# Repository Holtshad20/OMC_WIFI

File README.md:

# OMC WIFI

Proyecto de dispositivo medidor/protector conectado a una red a través de Wi-Fi y monitoreado con un servidor inicialmente interno a la red.

## Dispositivo medidor

### Hardware
Versión actual: 1.0\
Estado: Diseño PCB a la espera de enviar a fábrica.

**Listo**
- Diseño Esquemático KiCAD
- Diseño PCB KiCAD
- GERBERS

**Por hacer**
- Soldar componentes a PCB
- Realizar pruebas con software

Rango voltaje: 100 - 240 V RMS\
Máxima corriente: 20 A RMS - Limitado a 15 A con fusible

### Software
Versión actual: -\
Estado: Creación de códigos separados para posterior unificación.

#### Mediciones voltaje y corriente
Estado: A la espera de dispositivos que consuman mayor potencia para realizar más pruebas.

##### Listo
- Código medición voltaje y corriente.
- Realizar pruebas con distintos niveles de voltaje.

##### Por hacer
- Realizar pruebas con dispositivos que consuman mayor potencia (> 25W).

Rango voltaje: 70 - 240 V RMS\
Rango corriente: 0.2 - 15 A RMS\
*Nota:* Los mímimos en las lecturas se deben al ruido en la conversión AD. Es probable que se reduzca el ruido en PCB.

#### Accionamiento de relay
Estado: En proceso de desarrollo y pruebas

##### Listo
- Código de accionamiento de relay de acuerdo con nivel de voltaje.
- Realizar pruebas con valores de voltaje enviados por comunicación serial.
- Histéresis.

##### Por hacer
- Accionar relay cuando haya sobrecorriente
- Realizar pruebas con mediciones de voltaje real.
- Añadir inicio retardado para caso multidispositivo.

#### Configuración inicial - Conexión Dispositivo-Wi-Fi (AutoConnect)
Estado: En proceso de desarrollo y pruebas.

##### Listo
Por redactar

##### Por hacer
Por redactar

#### Conexión con servidor
Estado: No se ha iniciado.

##### Por hacer
- Implementación de MQTT

#### Integración de códigos
Estado: No se ha iniciado.
##### Por hacer
- Buscar forma de integrar usando FreeRTOS
- Comprobar funcionamiento de códigos integrados evitando interrupciones mutuas.

## Servidor
Estado: No se ha iniciado

**Por hacer**
- Implementación de MQTT en Raspberry Pi

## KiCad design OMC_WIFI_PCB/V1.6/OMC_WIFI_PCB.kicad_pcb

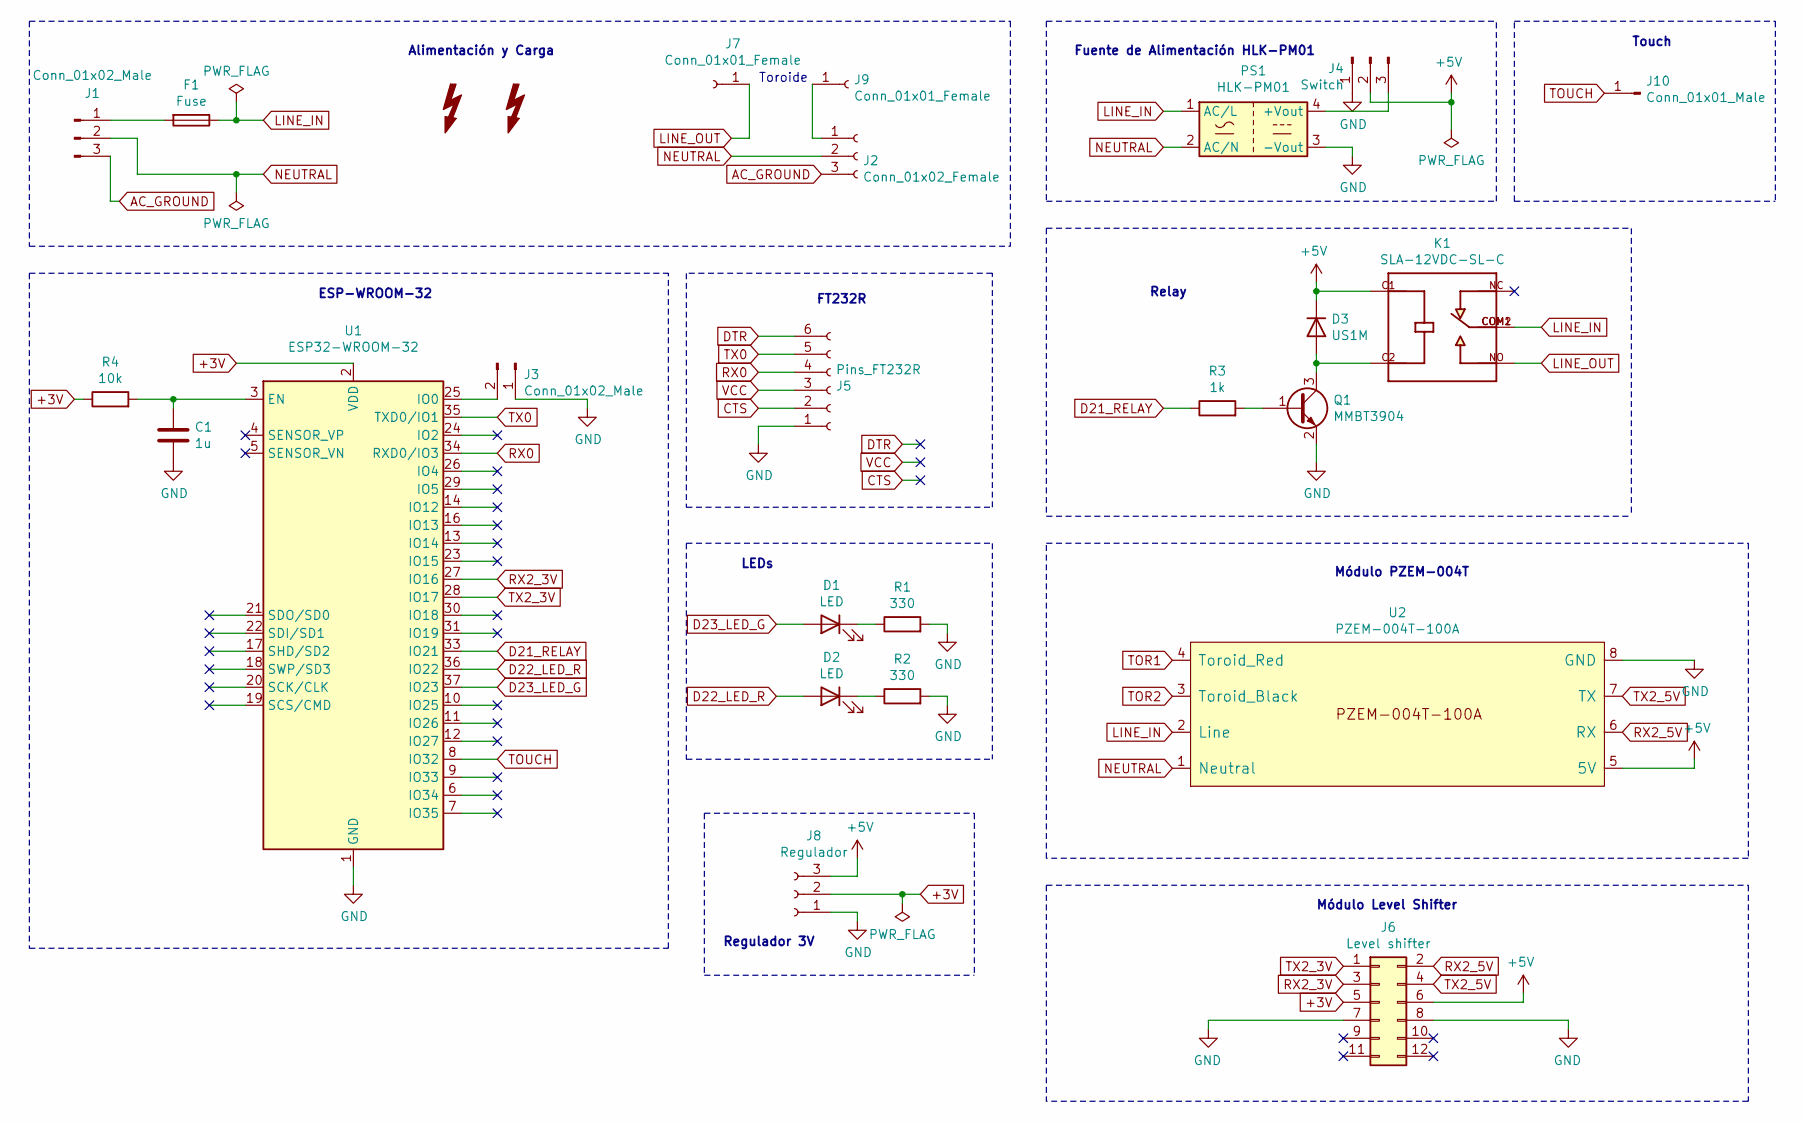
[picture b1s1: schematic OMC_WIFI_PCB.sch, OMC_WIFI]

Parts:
C1: 1u; C_0603_1608Metric_Pad1.08x0.95mm_HandSolder
D1, D2: LED; LED_0603_1608Metric_Pad1.05x0.95mm_HandSolder
D3: US1M; D_SMA
F1: Fuse; Fuseholder5x20_horiz_open_inline_Type-I
J1: Conn_01x02_Male; NEMA_5_P
J2: Conn_01x02_Female; NEMA_5_R
J3: Conn_01x02_Male; PinHeader_1x02_P2.54mm_Vertical
J4: Switch; PinHeader_1x03_P2.54mm_Vertical
J5: Pins_FT232R; PinSocket_1x06_P2.54mm_Vertical
J6: Level shifter; Level_Shifter_3V_5V
J7, J9: Conn_01x01_Female; SolderWire-1.5sqmm_1x01_D1.7mm_OD3mm
J8: Regulador; PinHeader_1x03_P2.54mm_Vertical
J10: Conn_01x01_Male; PinHeader_1x01_P2.54mm_Vertical
K1: SLA-12VDC-SL-C; RELAY_SLA-12VDC-SL-C
PS1: HLK-PM01; Converter_ACDC_HiLink_HLK-PMxx
Q1: MMBT3904; SOT-23
R1, R2: 330; R_0603_1608Metric_Pad0.98x0.95mm_HandSolder
R3: 1k; R_0603_1608Metric_Pad0.98x0.95mm_HandSolder
R4: 10k; R_0603_1608Metric_Pad0.98x0.95mm_HandSolder
SYM1, SYM2: SYM_Flash_Small; Symbol_HighVoltage_Type2_CopperTop_VerySmall
U1: ESP32-WROOM-32
U2: PZEM-004T-100A; PZEM-OO4T-100A

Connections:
+3V: J6.5, J8.2, R4.1, U1.2 (VDD)
+5V: D3.1 (K), J4.2, J6.6, J8.3, K1.C1, U2.5 (5V)
AC_GROUND: J1.3, J2.3
CTS: J5.2
D21_RELAY: R3.1, U1.33 (IO21)
D22_LED_R: D2.2 (A), U1.36 (IO22)
D23_LED_G: D1.2 (A), U1.37 (IO23)
DTR: J5.6
GND: C1.2, J3.1, J4.1, J5.1, J6.7, J6.8, J8.1, PS1.3 (-Vout), Q1.2 (E), R1.2, R2.2, U1.1 (GND), U1.15 (GND), U1.38 (GND), U1.39 (GND), U2.8 (GND)
LINE_IN: F1.1, K1.COM1, K1.COM2, PS1.1 (AC/L), U2.2 (Line)
LINE_OUT: J7.1, K1.NO
NEUTRAL: J1.2, J2.2, PS1.2 (AC/N), U2.1 (Neutral)
unnamed: C1.1, R4.2, U1.3 (EN)
unnamed: D1.1 (K), R1.1
unnamed: D2.1 (K), R2.1
unnamed: D3.2 (A), K1.C2, Q1.3 (C)
unnamed: F1.2, J1.1
unnamed: J2.1, J9.1
unnamed: J3.2, U1.25 (IO0)
unnamed: J4.3, PS1.4 (+Vout)
unnamed: Q1.1 (B), R3.2
RX0: J5.4, U1.34 (RXD0/IO3)
RX2_3V: J6.3, U1.27 (IO16)
RX2_5V: J6.2, U2.6 (RX)
TOR1: U2.4 (Toroid_Red)
TOR2: U2.3 (Toroid_Black)
TOUCH: J10.1, U1.8 (IO32)
TX0: J5.5, U1.35 (TXD0/IO1)
TX2_3V: J6.1, U1.28 (IO17)
TX2_5V: J6.4, U2.7 (TX)
VCC: J5.3

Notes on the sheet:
ESP-WROOM-32
Alimentación y Carga
LEDs
Fuente de Alimentación HLK-PM01
FT232R
Módulo Level Shifter
Regulador 3V
Módulo PZEM-004T
Relay
Toroide
Touch

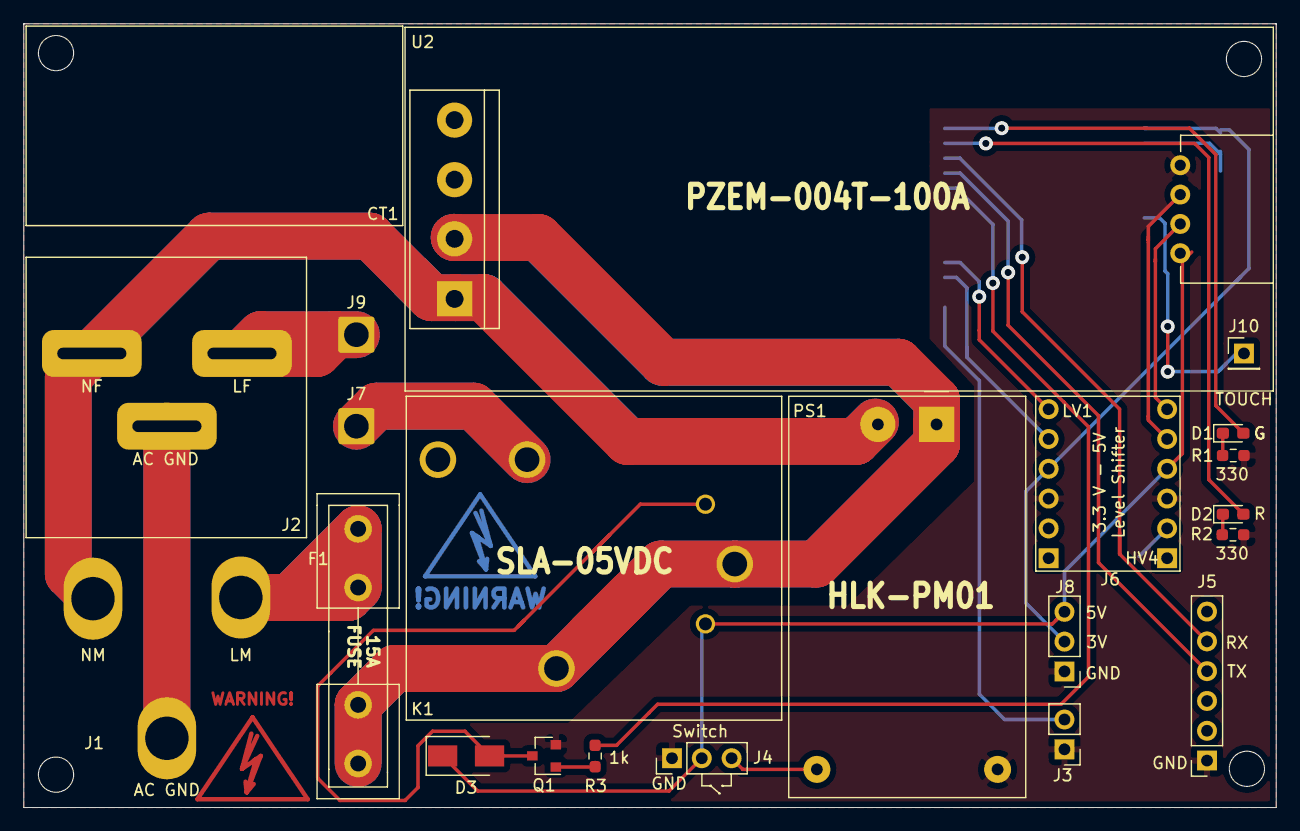
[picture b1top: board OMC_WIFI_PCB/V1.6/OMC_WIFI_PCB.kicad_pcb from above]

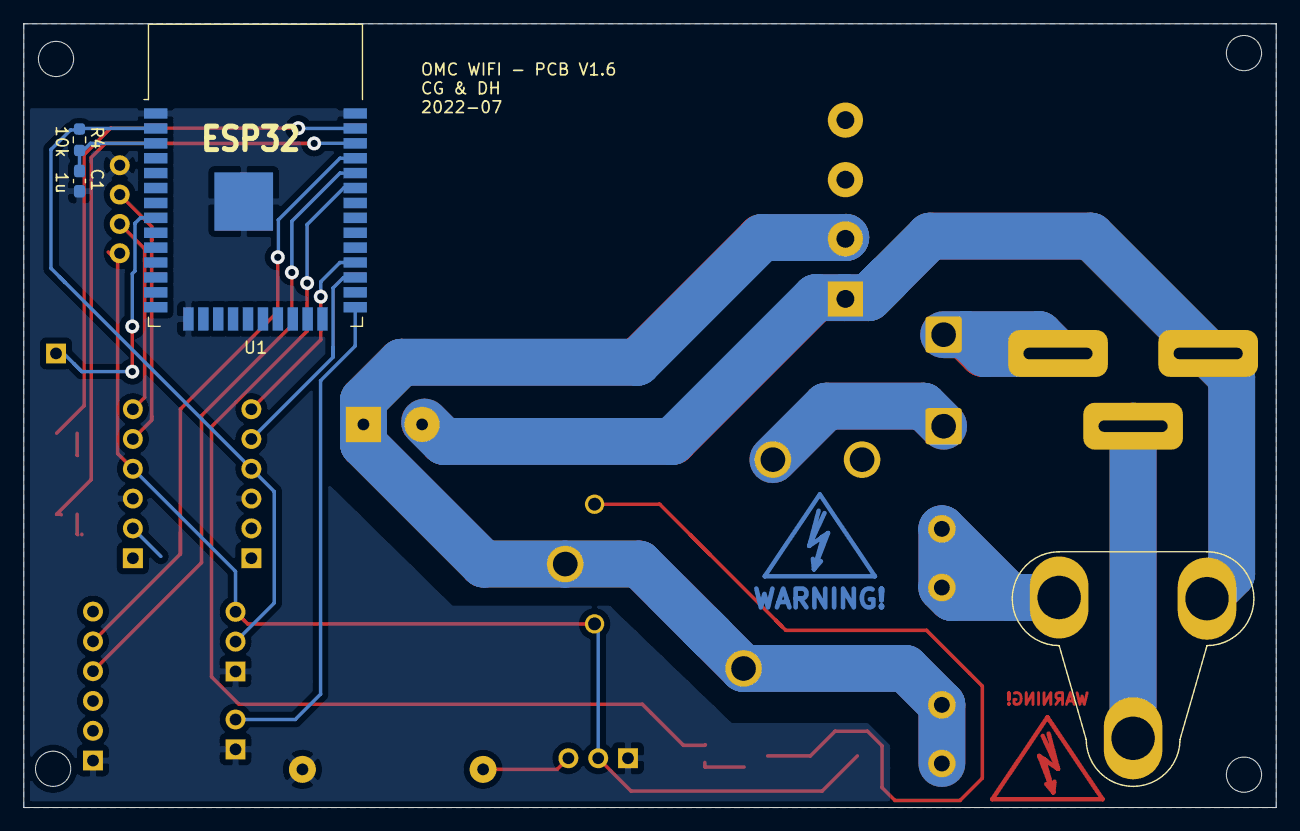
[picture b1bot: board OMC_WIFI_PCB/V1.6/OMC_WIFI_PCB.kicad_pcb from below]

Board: 2 copper layers, 106.8 x 66.8 mm, 26 parts (4 on the bottom side), 26 nets.

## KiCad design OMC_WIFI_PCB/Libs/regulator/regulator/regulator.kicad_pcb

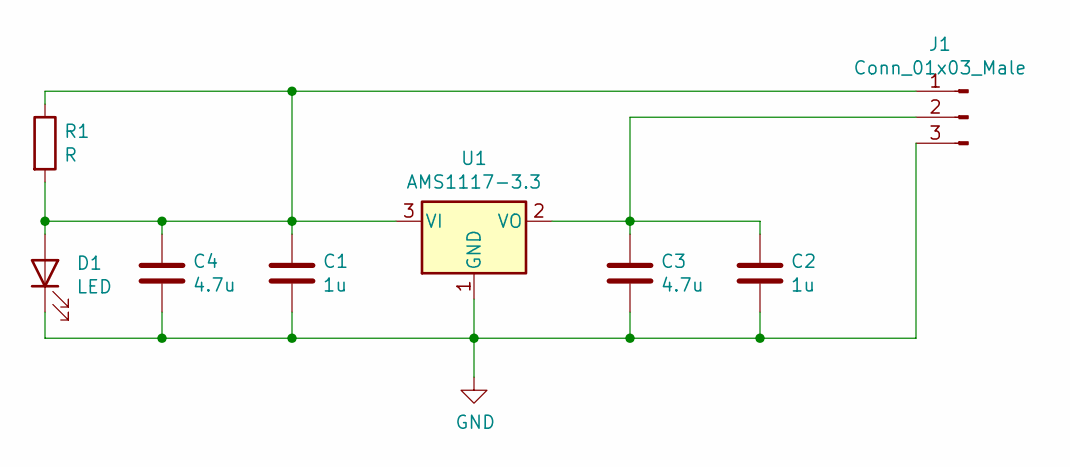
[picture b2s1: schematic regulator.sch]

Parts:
C1, C2: 1u; C_0603_1608Metric_Pad1.08x0.95mm_HandSolder
C3, C4: 4.7u; C_0805_2012Metric_Pad1.18x1.45mm_HandSolder
D1: LED; LED_0603_1608Metric_Pad1.05x0.95mm_HandSolder
J1: Conn_01x03_Male; PinHeader_1x03_P2.54mm_Horizontal
R1: R; R_0603_1608Metric_Pad0.98x0.95mm_HandSolder
U1: AMS1117-3.3; SOT-223-3_TabPin2

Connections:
GND: C1.2, C2.2, C3.2, C4.2, D1.1 (K), J1.3, U1.1 (GND)
unnamed: C1.1, C4.1, D1.2 (A), J1.1, R1.1, R1.2, U1.3 (VI)
unnamed: C2.1, C3.1, J1.2, U1.2 (VO)

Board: 2 copper layers, 8 parts (1 on the bottom side), 3 nets, no tracks yet.

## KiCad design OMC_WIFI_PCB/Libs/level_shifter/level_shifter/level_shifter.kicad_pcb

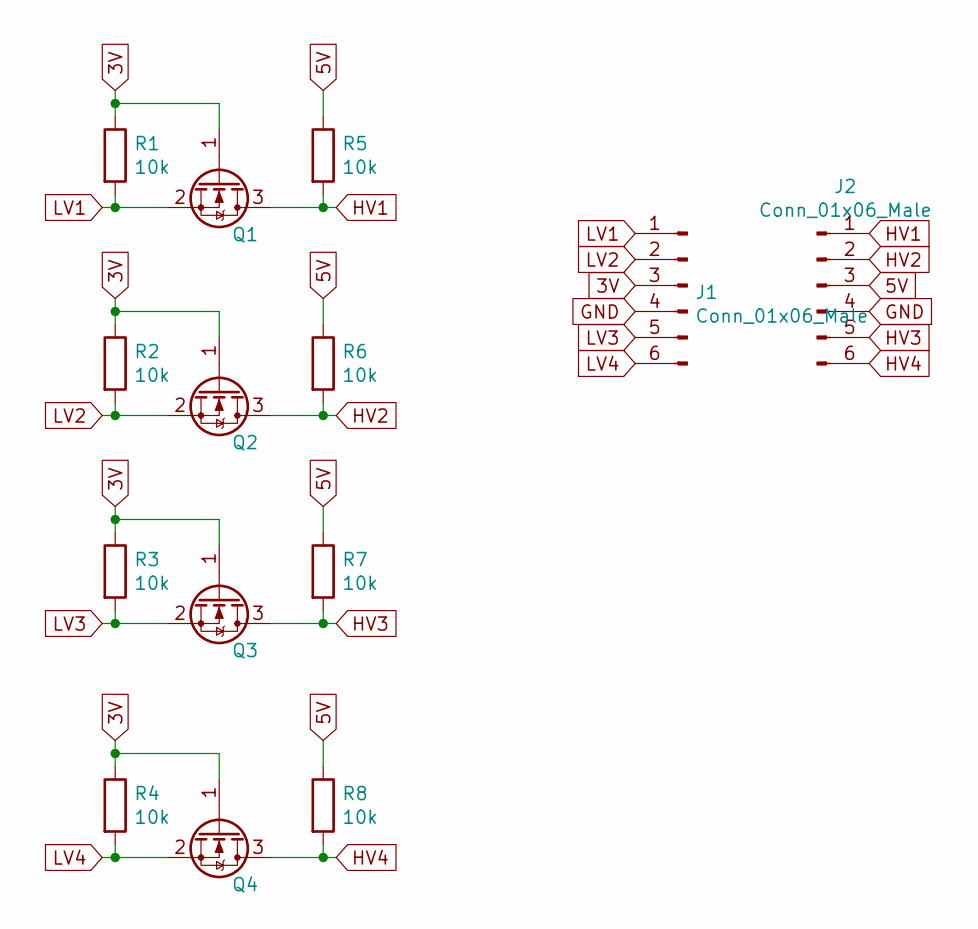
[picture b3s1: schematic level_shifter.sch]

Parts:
J1, J2: Conn_01x06_Male; PinHeader_1x06_P2.54mm_Vertical
Q1, Q2, Q3, Q4: BSS138; SOT-23
R1, R2, R3, R4, R5, R6, R7, R8: 10k; R_0603_1608Metric_Pad0.98x0.95mm_HandSolder

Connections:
3V: J1.3, Q1.1 (G), Q2.1 (G), Q3.1 (G), Q4.1 (G), R1.1, R2.1, R3.1, R4.1
5V: J2.3, R5.1, R6.1, R7.1, R8.1
GND: J1.4, J2.4
HV1: J2.1, Q1.3 (D), R5.2
HV2: J2.2, Q2.3 (D), R6.2
HV3: J2.5, Q3.3 (D), R7.2
HV4: J2.6, Q4.3 (D), R8.2
LV1: J1.1, Q1.2 (S), R1.2
LV2: J1.2, Q2.2 (S), R2.2
LV3: J1.5, Q3.2 (S), R3.2
LV4: J1.6, Q4.2 (S), R4.2

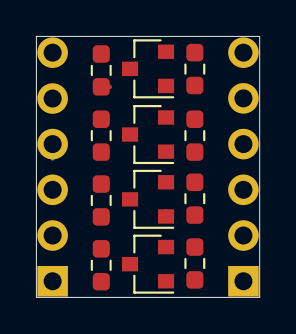
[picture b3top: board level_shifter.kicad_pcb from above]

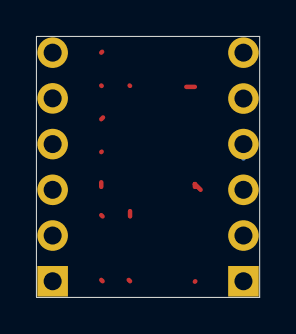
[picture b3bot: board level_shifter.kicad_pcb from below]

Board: 2 copper layers, 12.4 x 14.5 mm, 14 parts (2 on the bottom side), 11 nets.

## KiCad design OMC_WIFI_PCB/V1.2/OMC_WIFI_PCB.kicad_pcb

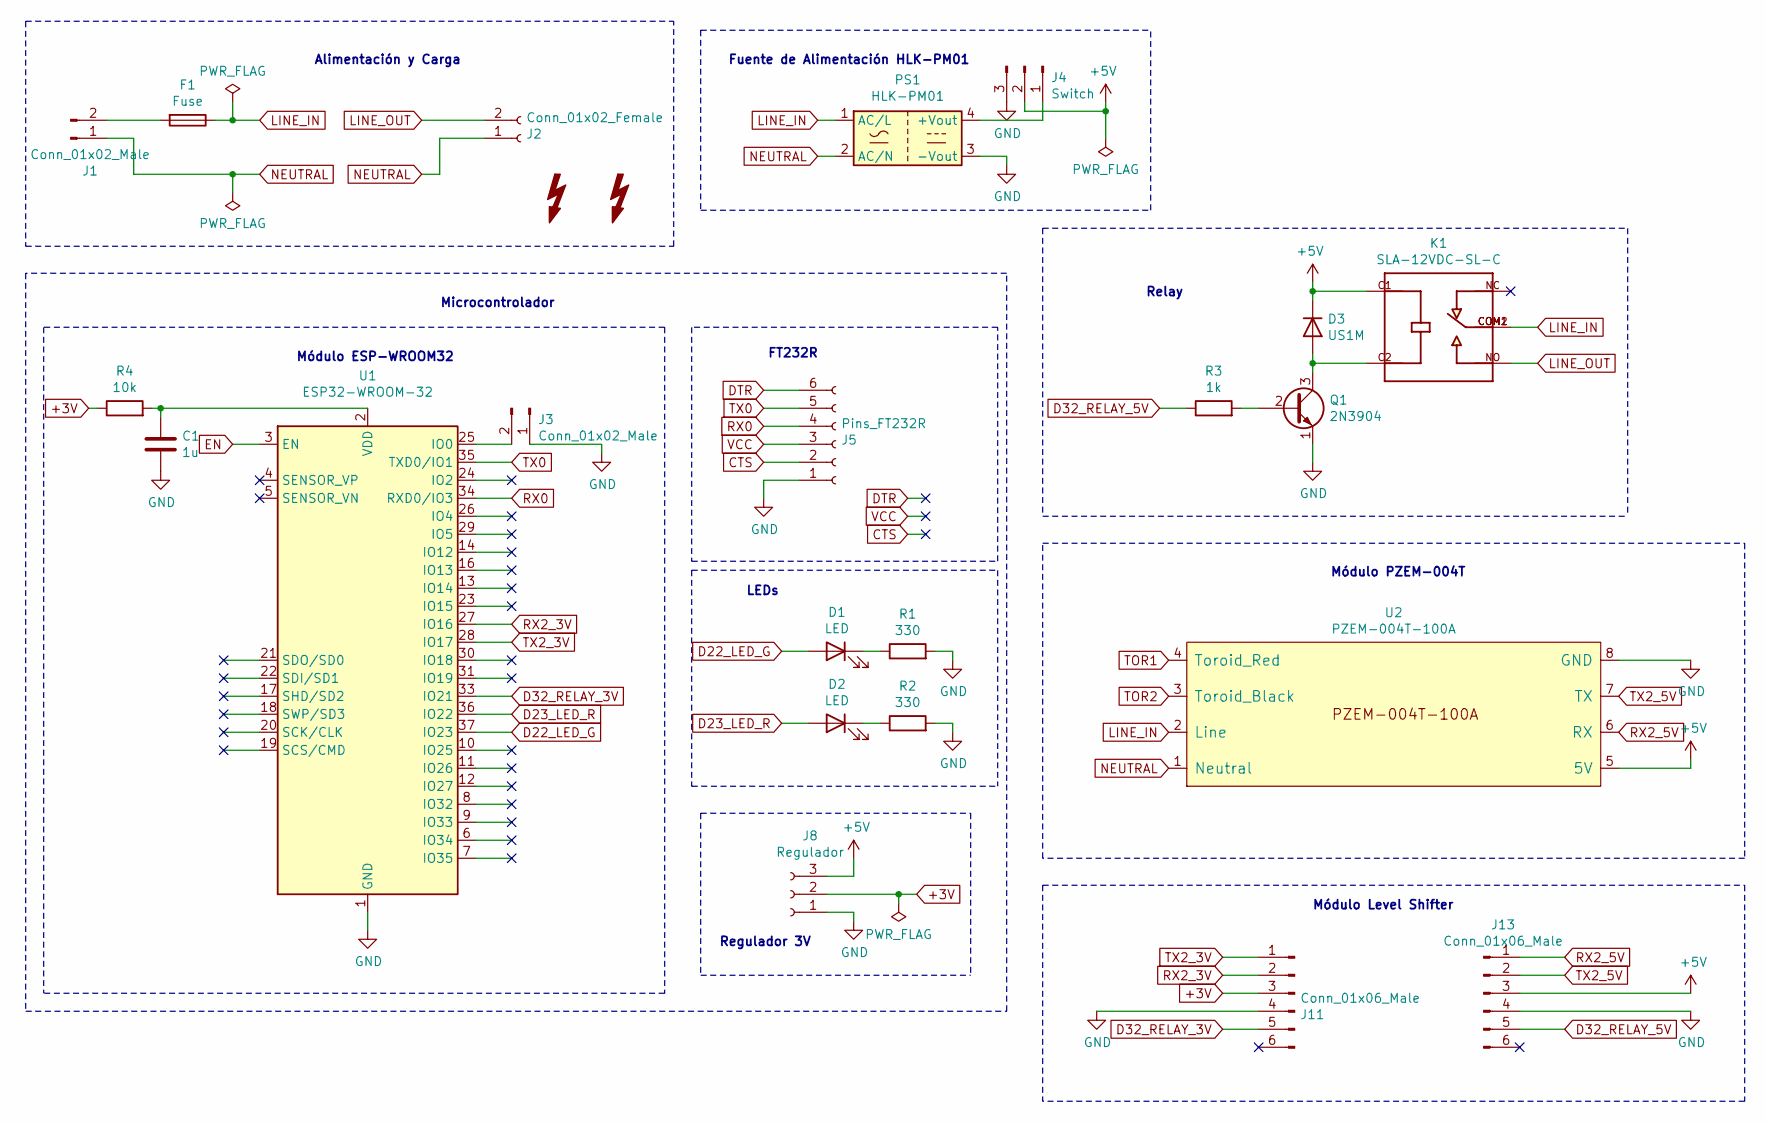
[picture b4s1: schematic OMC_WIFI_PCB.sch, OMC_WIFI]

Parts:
C1: 1u; C_0603_1608Metric_Pad1.08x0.95mm_HandSolder
D1, D2: LED; LED_0603_1608Metric_Pad1.05x0.95mm_HandSolder
D3: US1M; D_SMA
F1: Fuse; Fuseholder5x20_horiz_open_inline_Type-I
J1: Conn_01x02_Male; OMC-Male-Plug
J2: Conn_01x02_Female; OMC-Female-Plug
J3: Conn_01x02_Male; PinHeader_1x02_P2.54mm_Vertical
J4: Switch; SolderWire-0.75sqmm_1x03_P4.8mm_D1.25mm_OD2.3mm
J5: Pins_FT232R; PinSocket_1x06_P2.54mm_Vertical
J8: Regulador; PinHeader_1x03_P2.54mm_Vertical
J11, J13: Conn_01x06_Male; PinHeader_1x06_P2.54mm_Vertical
K1: SLA-12VDC-SL-C; RELAY_SLA-12VDC-SL-C
PS1: HLK-PM01; Converter_ACDC_HiLink_HLK-PMxx
Q1: 2N3904; SC-59_Handsoldering
R1, R2: 330; R_0603_1608Metric_Pad0.98x0.95mm_HandSolder
R3: 1k; R_0603_1608Metric_Pad0.98x0.95mm_HandSolder
R4: 10k; R_0603_1608Metric_Pad0.98x0.95mm_HandSolder
SYM1, SYM2: SYM_Flash_Small; Symbol_HighVoltage_Type2_CopperTop_VerySmall
U1: ESP32-WROOM-32
U2: PZEM-004T-100A; PZEM-OO4T-100A

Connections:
+3V: J8.2, J11.3, R4.1
+5V: D3.1 (K), J4.2, J8.3, J13.3, K1.C1, U2.5 (5V)
CTS: J5.2
D22_LED_G: D1.2 (A), U1.37 (IO23)
D23_LED_R: D2.2 (A), U1.36 (IO22)
D32_RELAY_3V: J11.5, U1.33 (IO21)
D32_RELAY_5V: J13.5, R3.1
DTR: J5.6
EN: U1.3 (EN)
GND: C1.2, J3.1, J4.3, J5.1, J8.1, J11.4, J13.4, PS1.3 (-Vout), Q1.1 (E), R1.2, R2.2, U1.1 (GND), U1.15 (GND), U1.38 (GND), U1.39 (GND), U2.8 (GND)
LINE_IN: F1.1, K1.COM1, K1.COM2, PS1.1 (AC/L), U2.2 (Line)
LINE_OUT: J2.2, K1.NO
NEUTRAL: J1.1, J2.1, PS1.2 (AC/N), U2.1 (Neutral)
unnamed: C1.1, R4.2, U1.2 (VDD)
unnamed: D1.1 (K), R1.1
unnamed: D2.1 (K), R2.1
unnamed: D3.2 (A), K1.C2, Q1.3 (C)
unnamed: F1.2, J1.2
unnamed: J3.2, U1.25 (IO0)
unnamed: J4.1, PS1.4 (+Vout)
unnamed: Q1.2 (B), R3.2
RX0: J5.4, U1.34 (RXD0/IO3)
RX2_3V: J11.2, U1.27 (IO16)
RX2_5V: J13.1, U2.6 (RX)
TOR1: U2.4 (Toroid_Red)
TOR2: U2.3 (Toroid_Black)
TX0: J5.5, U1.35 (TXD0/IO1)
TX2_3V: J11.1, U1.28 (IO17)
TX2_5V: J13.2, U2.7 (TX)
VCC: J5.3

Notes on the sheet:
Módulo ESP-WROOM32
Alimentación y Carga
Relay
LEDs
Fuente de Alimentación HLK-PM01
FT232R
Microcontrolador
Módulo PZEM-004T
Módulo Level Shifter
Regulador 3V

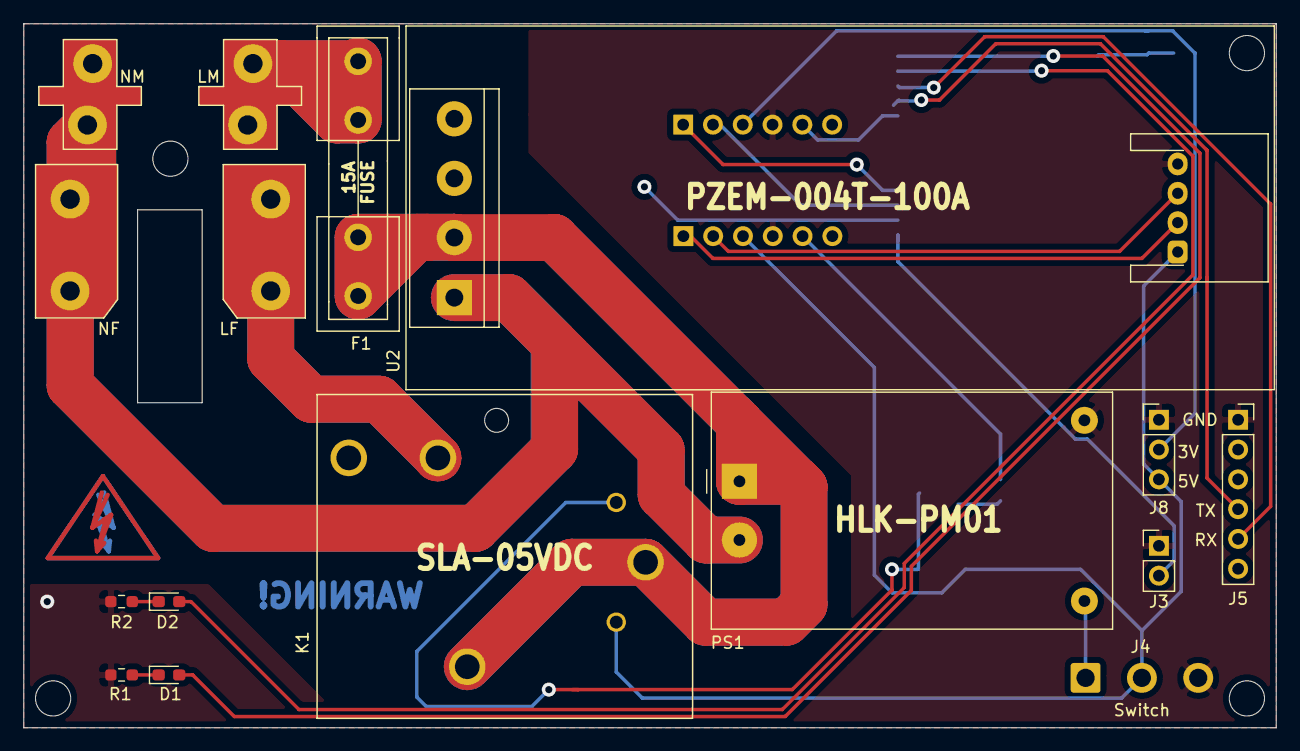
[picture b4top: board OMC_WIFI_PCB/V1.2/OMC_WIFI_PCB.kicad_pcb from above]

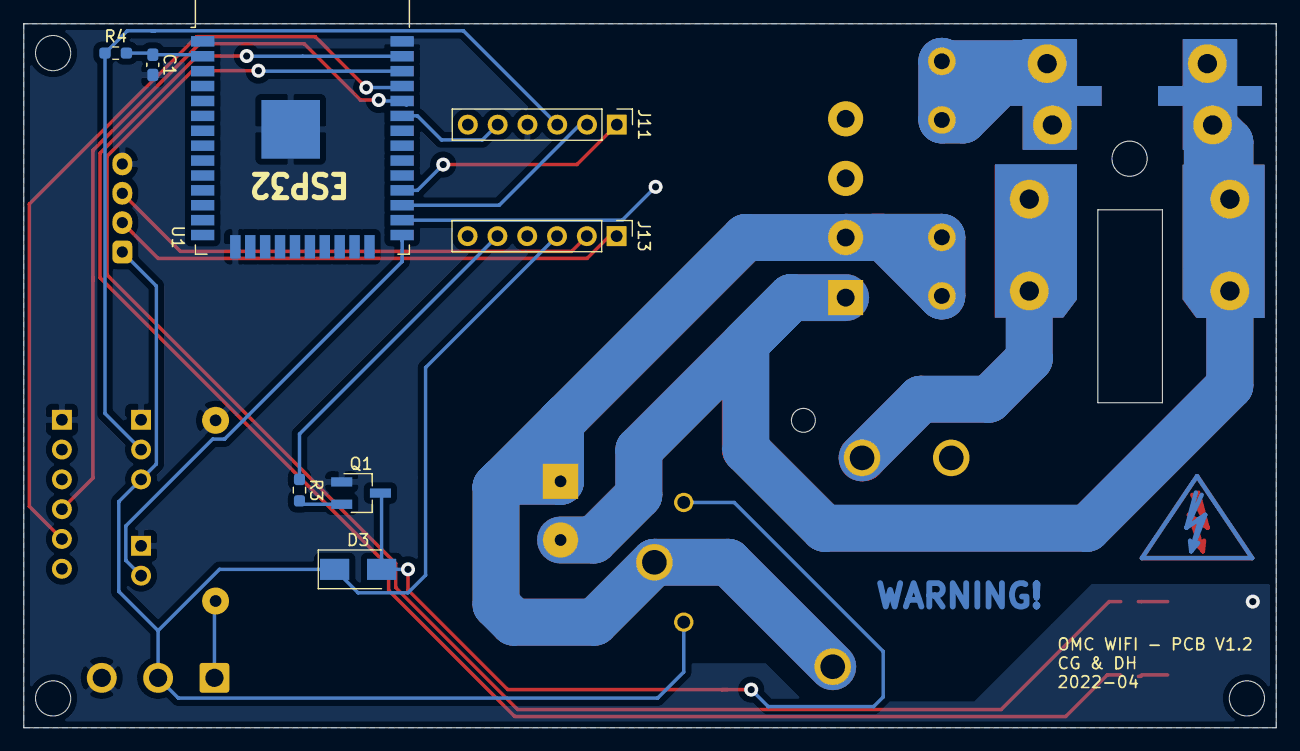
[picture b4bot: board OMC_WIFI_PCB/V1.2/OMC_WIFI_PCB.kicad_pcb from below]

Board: 2 copper layers, 106.8 x 60.0 mm, 24 parts (9 on the bottom side), 24 nets.

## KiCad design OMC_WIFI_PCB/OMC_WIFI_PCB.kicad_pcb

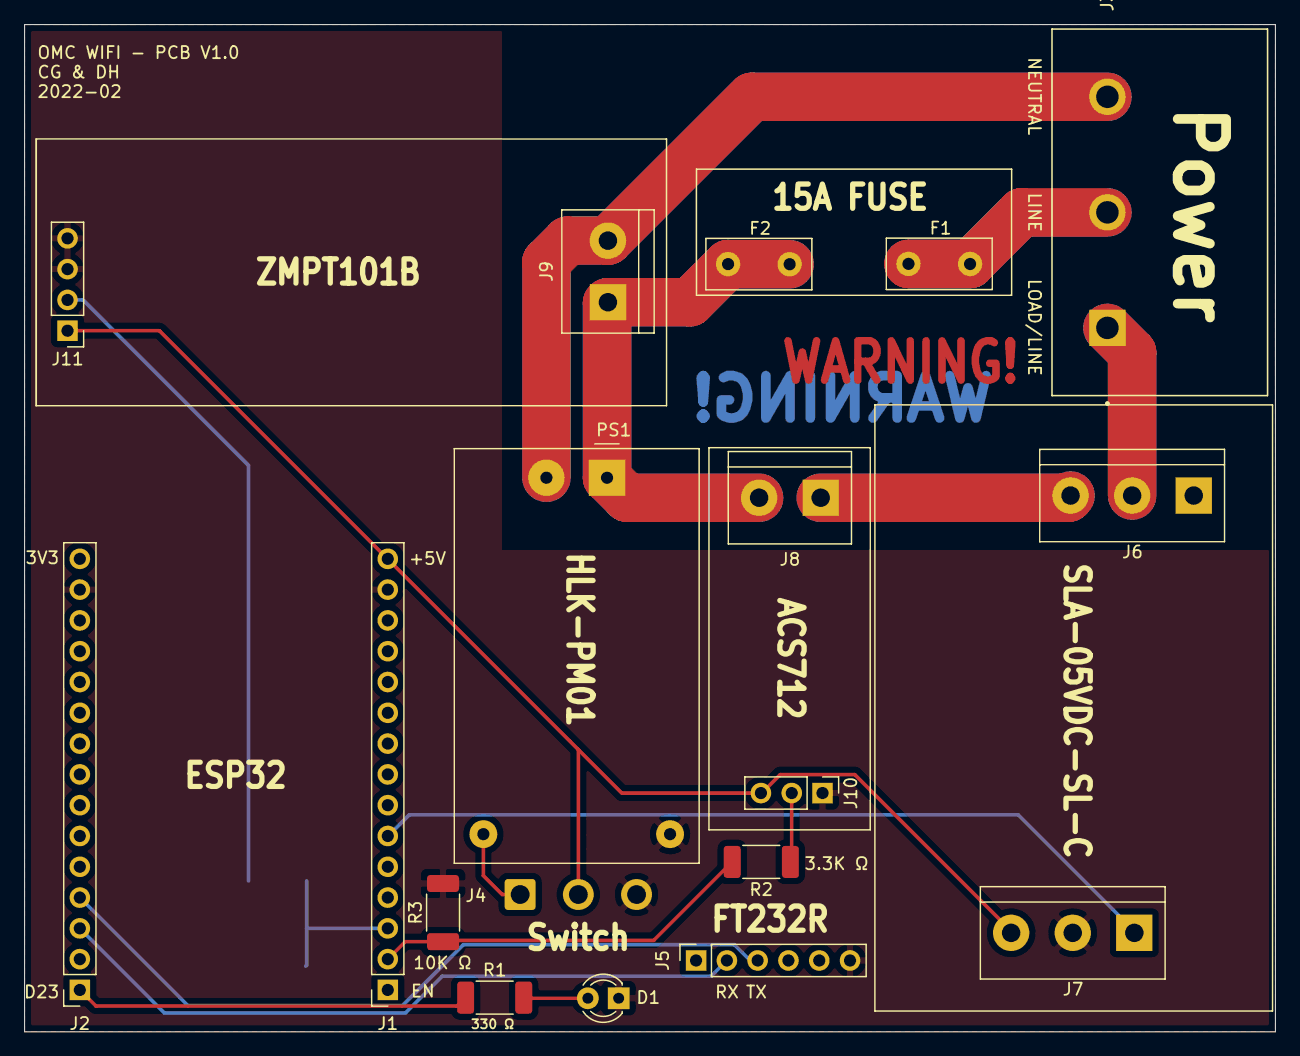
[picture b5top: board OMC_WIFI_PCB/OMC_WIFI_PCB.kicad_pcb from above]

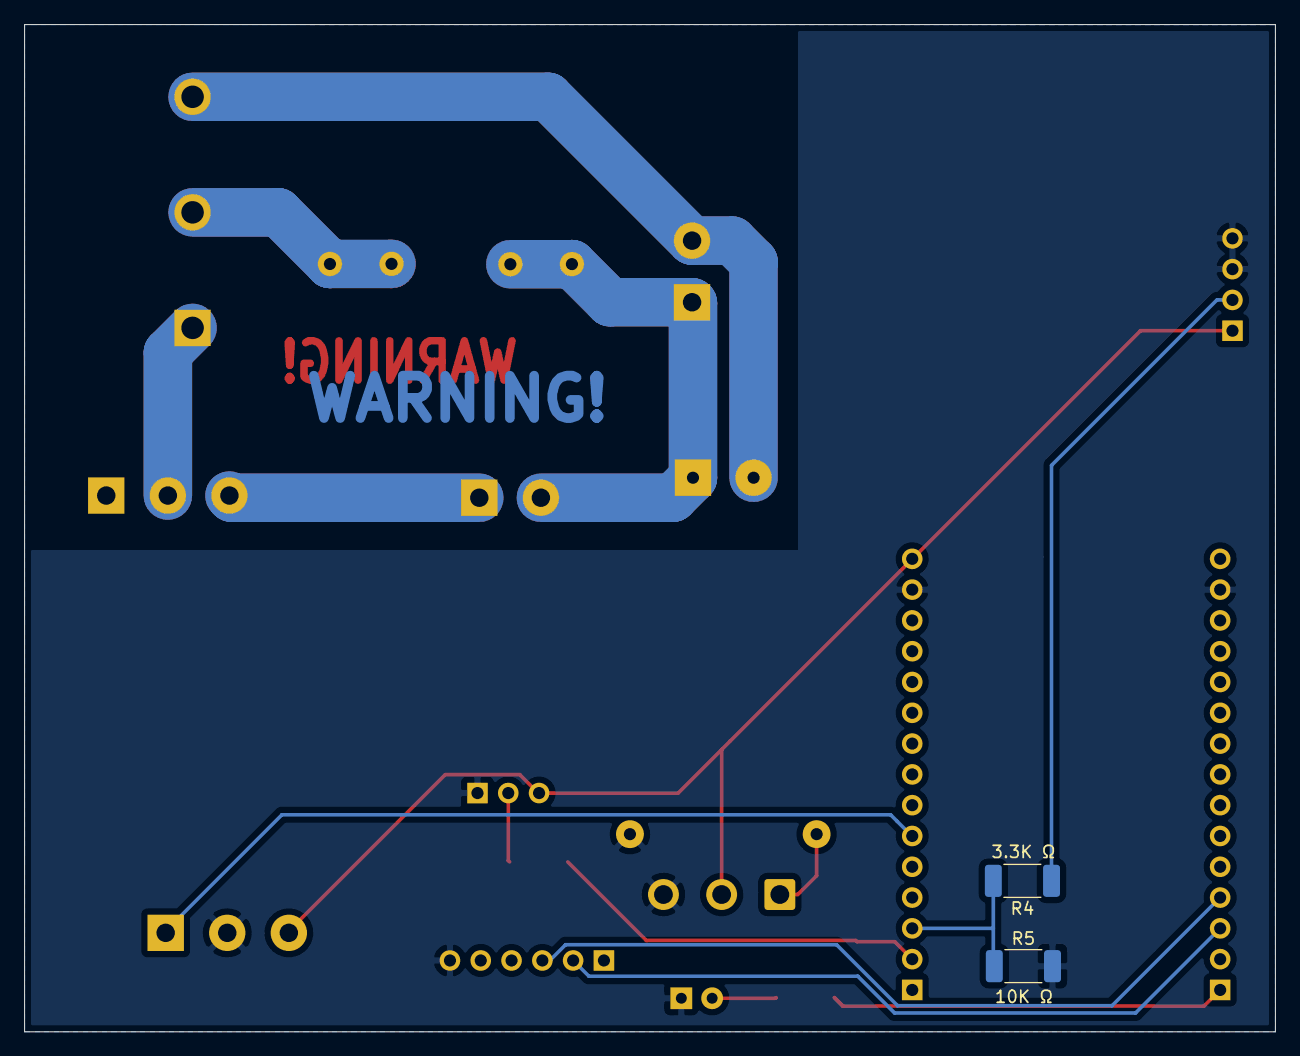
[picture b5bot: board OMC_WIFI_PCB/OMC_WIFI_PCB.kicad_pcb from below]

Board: 2 copper layers, 103.2 x 83.1 mm, 20 parts (2 on the bottom side), 17 nets.

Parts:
D1: LED; LED_D3.0mm
F1, F2: Fuse; Fuse_Littelfuse_395Series
J1: ESP32_Left; PinSocket_1x15_P2.54mm_Vertical
J2: ESP32_Right; PinSocket_1x15_P2.54mm_Vertical
J3: Power_In; TE_5-1437652-4
J4: Switch; SolderWire-0.75sqmm_1x03_P4.8mm_D1.25mm_OD2.3mm
J5: Pins_FT232R; PinSocket_1x06_P2.54mm_Vertical
J6: Line_Relay; TerminalBlock_bornier-3_P5.08mm
J7: Control_Relay; TerminalBlock_bornier-3_P5.08mm
J8: Line_ACS712; TerminalBlock_bornier-2_P5.08mm
J9: Line_ZMPT101B; TerminalBlock_bornier-2_P5.08mm
J10: Control_ACS712; PinHeader_1x03_P2.54mm_Vertical
J11: Control_ZMPT101B; PinHeader_1x04_P2.54mm_Vertical
PS1: HLK-PM01; Converter_ACDC_HiLink_HLK-PMxx
R1: 330; R_2010_5025Metric_Pad1.40x2.65mm_HandSolder
R2, R4: 3.3K; R_2010_5025Metric_Pad1.40x2.65mm_HandSolder
R3, R5: 10K; R_2010_5025Metric_Pad1.40x2.65mm_HandSolder

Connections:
+5V: J1.15, J4.2, J7.3, J10.3, J11.1
COM: J3.1, J6.2
D23_LED: J2.1, R1.1
D32_RELAY: J1.6, J7.1
GND: D1.1, J1.14, J2.14, J4.3, J5.6, J7.2, J10.1, J11.3, J11.4, PS1.3, R3.2, R5.2
LINE: F2.1, F2.2, J8.2, J9.1, PS1.1
NEUTRAL: J3.3, J9.2, PS1.2
NO: J6.3, J8.1
unnamed: D1.2, R1.2
unnamed: F1.1, F1.2, J3.2
unnamed: J4.1, PS1.4
unnamed: J10.2, R2.1
unnamed: J11.2, R4.1
RX0: J2.4, J5.3
TX0: J2.3, J5.2
VN_ZMPT: J1.3, R4.2, R5.1
VP_ACS: J1.2, R2.2, R3.1

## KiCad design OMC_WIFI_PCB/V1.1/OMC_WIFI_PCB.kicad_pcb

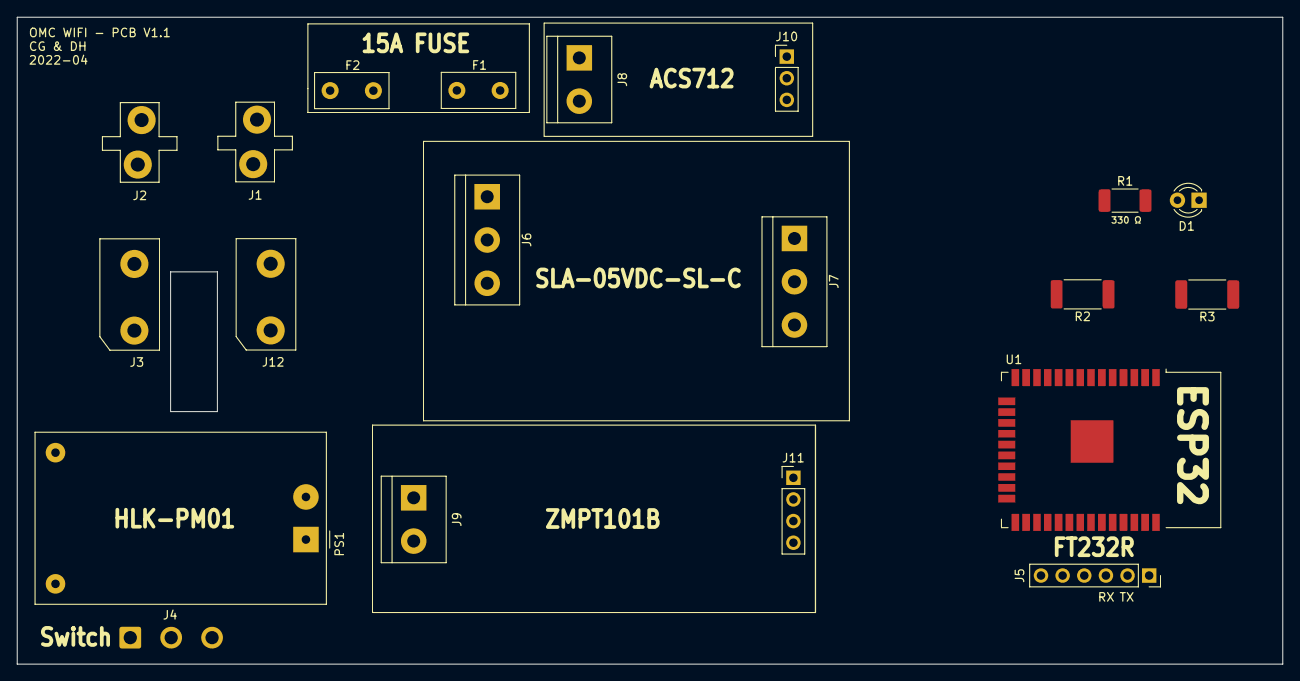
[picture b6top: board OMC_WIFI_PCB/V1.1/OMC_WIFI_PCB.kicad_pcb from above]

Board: 2 copper layers, 148.6 x 75.9 mm, 20 parts (0 on the bottom side), 16 nets.

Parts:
D1: LED; LED_D3.0mm
F1, F2: Fuse; Fuse_Littelfuse_395Series
J1: Line Input; OMC-Male-Plug
J2: Nuetral Input; OMC-Male-Plug
J3: Line Output; OMC-Female-Plug
J4: Switch; SolderWire-0.75sqmm_1x03_P4.8mm_D1.25mm_OD2.3mm
J5: Pins_FT232R; PinSocket_1x06_P2.54mm_Vertical
J6: Line_Relay; TerminalBlock_bornier-3_P5.08mm
J7: Control_Relay; TerminalBlock_bornier-3_P5.08mm
J8: Line_ACS712; TerminalBlock_bornier-2_P5.08mm
J9: Line_ZMPT101B; TerminalBlock_bornier-2_P5.08mm
J10: Control_ACS712; PinHeader_1x03_P2.54mm_Vertical
J11: Control_ZMPT101B; PinHeader_1x04_P2.54mm_Vertical
J12: Nuetral Output; OMC-Female-Plug
PS1: HLK-PM01; Converter_ACDC_HiLink_HLK-PMxx
R1: 330; R_2010_5025Metric_Pad1.40x2.65mm_HandSolder
R2: 1K; R_2512_6332Metric_Pad1.40x3.35mm_HandSolder
R3: 2K; R_2512_6332Metric_Pad1.40x3.35mm_HandSolder
U1: ESP32-WROOM-32

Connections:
+5V: J4.2, J7.3, J10.3, J11.1, R2.2
D23_LED: R1.1, U1.37
D32_RELAY: J7.1, U1.8
GND: D1.1, J4.3, J5.6, J7.2, J10.1, J11.3, J11.4, PS1.3, R3.1, U1.1, U1.15, U1.38, U1.39
LINE: F2.1, F2.2, J8.2, J9.1
NEUTRAL: J2.1, J9.2
NO: J6.3, J8.1
unnamed: D1.2, R1.2
unnamed: F1.1, F1.2, J1.1
unnamed: J4.1, PS1.4
unnamed: R2.1, R3.2, U1.2
Neutral: J12.1, PS1.1
RX0: J5.3, U1.34
TX0: J5.2, U1.35
VN_ZMPT: J11.2, U1.5
VP_ACS: J10.2, U1.4

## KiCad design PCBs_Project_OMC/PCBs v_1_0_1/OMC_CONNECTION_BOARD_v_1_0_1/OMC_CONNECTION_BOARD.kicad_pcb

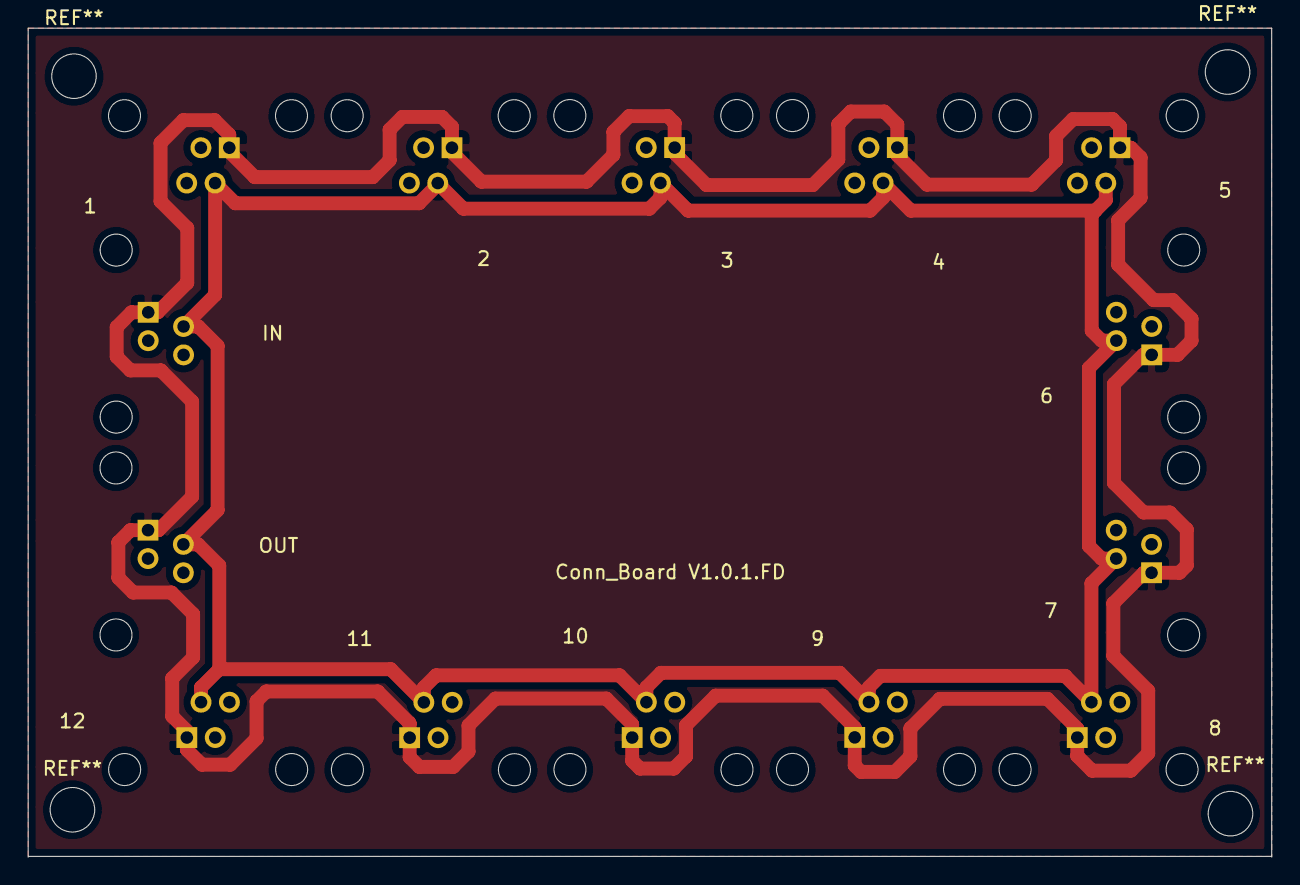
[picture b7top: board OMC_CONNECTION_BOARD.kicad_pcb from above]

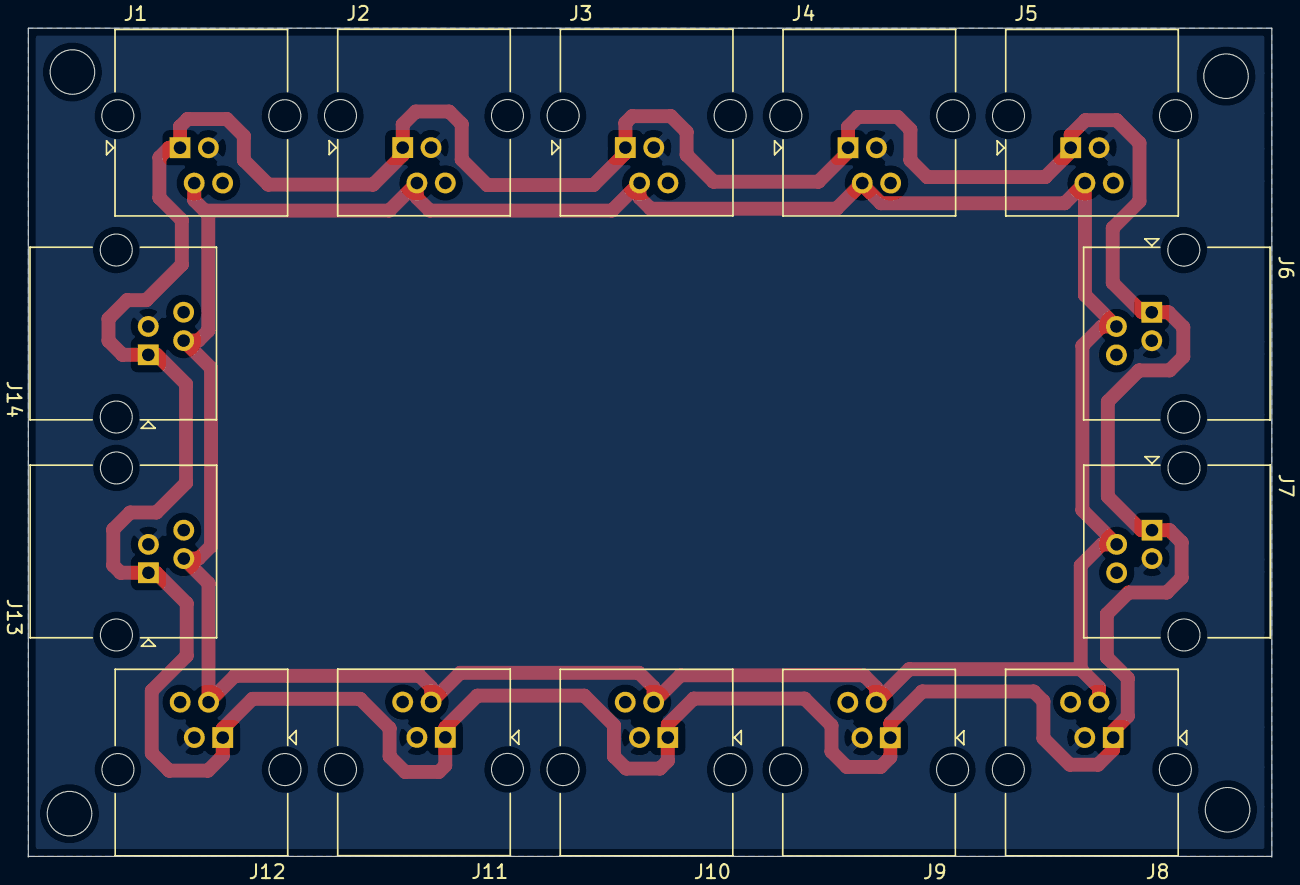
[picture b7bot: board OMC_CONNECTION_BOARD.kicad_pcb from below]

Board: 2 copper layers, 89.4 x 59.6 mm, 14 parts (14 on the bottom side), 3 nets.

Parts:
J1, J2, J3, J4, J5, J6, J7, J8, J9, J10, J11, J12, J13, J14: RJ14; RJ14_Connfly_DS1133-S4_Horizontal

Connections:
GND: J1.3, J2.3, J3.3, J4.3, J5.3, J6.3, J7.3, J8.3, J9.3, J10.3, J11.3, J12.3, J13.3, J14.3
H: J1.1, J2.1, J3.1, J4.1, J5.1, J6.1, J7.1, J8.1, J9.1, J10.1, J11.1, J12.1, J13.1, J14.1
L: J1.2, J2.2, J3.2, J4.2, J5.2, J6.2, J7.2, J8.2, J9.2, J10.2, J11.2, J12.2, J13.2, J14.2
